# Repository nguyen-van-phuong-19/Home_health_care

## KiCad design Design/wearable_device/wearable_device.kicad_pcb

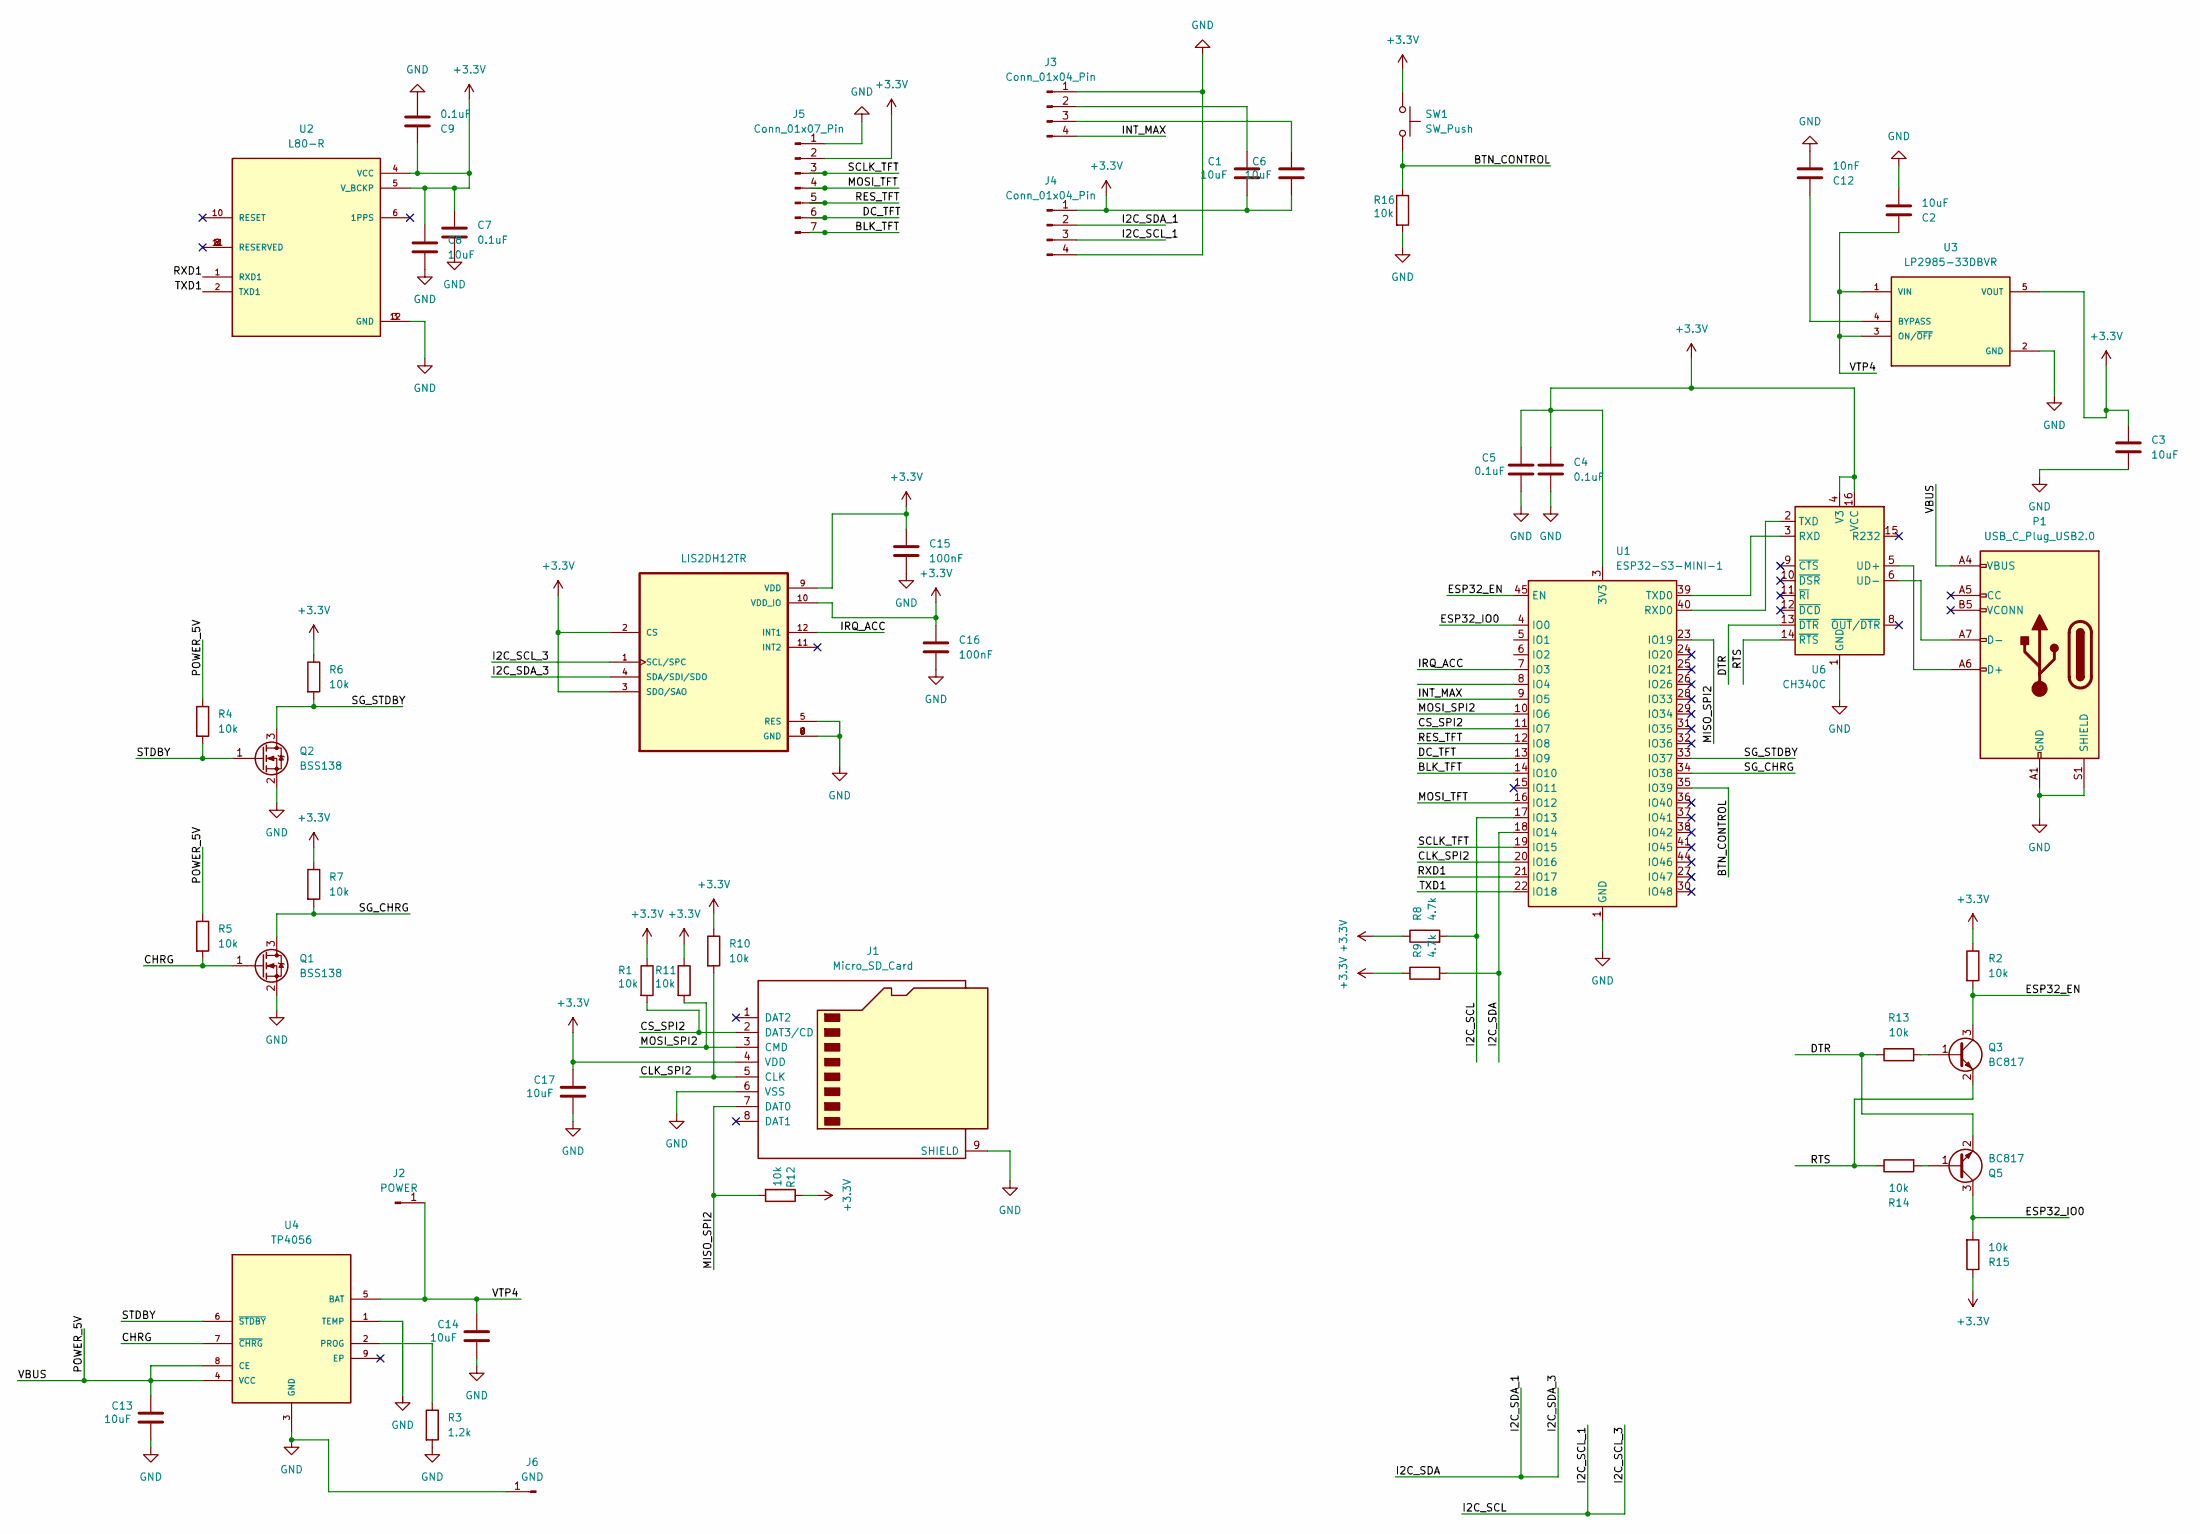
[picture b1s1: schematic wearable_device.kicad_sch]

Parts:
C1, C2, C3, C6, C8, C13, C14, C17: 10uF; C_0603_1608Metric
C4, C5, C7, C9: 0.1uF; C_0603_1608Metric
C12: 10nF; C_0603_1608Metric
C15, C16: 100nF; C_0603_1608Metric
J1: Micro_SD_Card; microSD_HC_Hirose_DM3D-SF
J2: POWER; PinHeader_1x01_P2.00mm_Vertical
J3, J4: Conn_01x04_Pin; PinHeader_1x04_P2.00mm_Vertical
J5: Conn_01x07_Pin; PinHeader_1x07_P2.54mm_Vertical
J6: GND; PinHeader_1x01_P2.00mm_Vertical
P1: USB_C_Plug_USB2.0; USB_C_Receptacle_GCT_USB4105-xx-A_16P_TopMnt_Horizontal
Q1, Q2: BSS138; SOT-23
Q3, Q5: BC817; SOT-23
R1, R2, R4, R5, R6, R7, R10, R11, R12, R13, R14, R15, R16: 10k; R_0603_1608Metric
R3: 1.2k; R_0603_1608Metric
R8, R9: 4.7k; R_0603_1608Metric
SW1: SW_Push; SW_Tactile_SPST_NO_Straight_CK_PTS636Sx25SMTRLFS
U1: ESP32-S3-MINI-1; ESP32-S2-MINI-1
U2: L80-R; XCVR_L80-R
U3: LP2985-33DBVR; SOT95P280X145-5N; PARTREV O
U4: TP4056; SOP127P600X175-9N
U5: LIS2DH12TR; PQFN50P200X200100-12N
U6: CH340C; SOIC-16_3.9x9.9mm_P1.27mm

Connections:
+3.3V: C1.2, C3.1, C4.1, C5.1, C6.2, C7.1, C8.1, C9.1, C15.1, C16.1, C17.1, J1.4 (VDD), J4.1, J5.2, R1.1, R2.1, R6.1, R7.1, R8.1, R9.1, R10.1, R11.1, R12.1, R15.1, SW1.1, U1.3 (3V3), U2.4 (VCC), U2.5 (V_BCKP), U3.5 (VOUT), U5.2 (CS), U5.3 (SDO/SAO), U5.9 (VDD), U5.10 (VDD_IO), U6.4 (V3), U6.16 (VCC)
/BLK_TFT: J5.7, U1.14 (IO10)
/BTN_CONTROL: R16.1, SW1.2, U1.35 (IO39)
/CHRG: Q1.1 (G), R5.2, U4.7 (~CHRG)
/CLK_SPI2: J1.5 (CLK), R10.2, U1.20 (IO16)
/CS_SPI2: J1.2 (DAT3/CD), R1.2, U1.11 (IO7)
/DC_TFT: J5.6, U1.13 (IO9)
/DTR: Q5.2 (E), R13.1, U6.13 (~DTR)
/ESP32_EN: Q3.3 (C), R2.2, U1.45 (EN)
/ESP32_IO0: Q5.3 (C), R15.2, U1.4 (IO0)
/I2C_SCL: J4.3, R8.2, U1.17 (IO13), U5.1 (SCL/SPC)
/I2C_SDA: J4.2, R9.2, U1.18 (IO14), U5.4 (SDA/SDI/SDO)
/INT_MAX: J3.4, U1.9 (IO5)
/IRQ_ACC: U1.7 (IO3), U5.12 (INT1)
/MISO_SPI2: J1.7 (DAT0), R12.2, U1.23 (IO19)
/MOSI_SPI2: J1.3 (CMD), R11.2, U1.10 (IO6)
/MOSI_TFT: J5.4, U1.16 (IO12)
/POWER_5V: C13.1, P1.A4 (VBUS), P1.A9 (VBUS), P1.B4 (VBUS), P1.B9 (VBUS), R4.1, R5.1, U4.4 (VCC), U4.8 (CE)
/RES_TFT: J5.5, U1.12 (IO8)
/RTS: Q3.2 (E), R14.1, U6.14 (~RTS)
/RXD1: U1.21 (IO17), U2.1 (RXD1)
/SCLK_TFT: J5.3, U1.19 (IO15)
/SG_CHRG: Q1.3 (D), R7.2, U1.34 (IO38)
/SG_STDBY: Q2.3 (D), R6.2, U1.33 (IO37)
/STDBY: Q2.1 (G), R4.2, U4.6 (~STDBY)
/TXD1: U1.22 (IO18), U2.2 (TXD1)
/VTP4: C2.1, C14.1, J2.1, U3.1 (VIN), U3.3 (ON/~OFF), U4.5 (BAT)
GND: C2.2, C3.2, C4.2, C5.2, C7.2, C8.2, C9.2, C12.2, C13.2, C14.2, C15.2, C16.2, C17.2, J1.6 (VSS), J1.9 (SHIELD), J3.1, J4.4, J5.1, J6.1, P1.A1 (GND), P1.A12 (GND), P1.B1 (GND), P1.B12 (GND), P1.S1 (SHIELD), Q1.2 (S), Q2.2 (S), R3.2, R16.2, U1.1 (GND), U1.2 (GND), U1.42 (GND), U1.43 (GND), U1.46 (GND), U1.47 (GND), U1.48 (GND), U1.49 (GND), U1.50 (GND), U1.51 (GND), U1.52 (GND), U1.53 (GND), U1.54 (GND), U1.55 (GND), U1.56 (GND), U1.57 (GND), U1.58 (GND), U1.59 (GND), U1.60 (GND), U1.61 (GND), U1.62 (GND), U1.63 (GND), U1.64 (GND), U1.65 (GND), U2.3 (GND), U2.12 (GND), U3.2 (GND), U4.1 (TEMP), U4.3 (GND), U5.5 (RES), U5.6 (GND), U5.7 (GND), U5.8 (GND), U6.1 (GND)
unnamed: C1.1, J3.2
unnamed: C6.1, J3.3
unnamed: P1.A6 (D+), U6.5 (UD+)
unnamed: P1.A7 (D-), U6.6 (UD-)
unnamed: Q3.1 (B), R13.2
unnamed: Q5.1 (B), R14.2
unnamed: U1.40 (RXD0), U6.2 (TXD)
unnamed: U1.39 (TXD0), U6.3 (RXD)
unnamed: C12.1, U3.4 (BYPASS)
unnamed: R3.1, U4.2 (PROG)

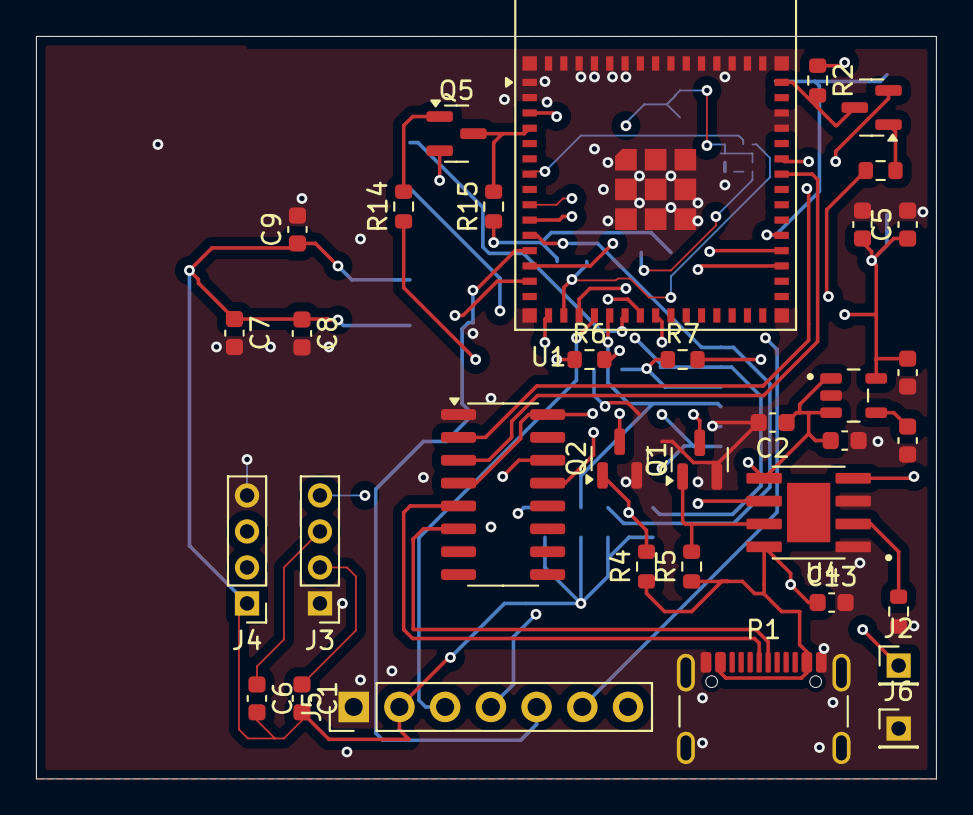
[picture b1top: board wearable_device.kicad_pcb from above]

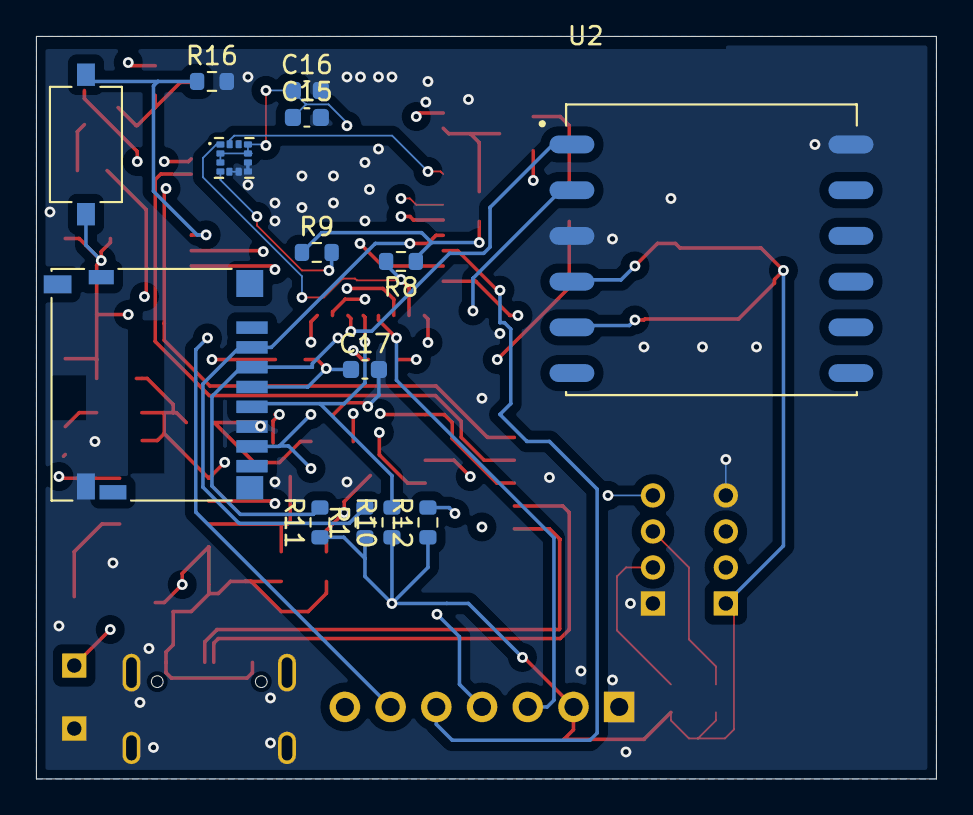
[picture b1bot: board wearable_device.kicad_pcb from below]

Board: 4 copper layers, 50.0 x 41.2 mm, 49 parts (14 on the bottom side), 38 nets.

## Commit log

2025-01-27 add documents form windown
    and add project to windown
2025-02-07 create server project
2025-02-07 add requirements context
2025-02-07 add gitignore file
2025-02-08 add openai library
2025-02-11 add 2 folder to github
2025-02-21 add design wearable device
2025-03-03 add design
2025-03-03 hello
2025-03-03 add .gitignore to exclude build artifacts and configuration files
2025-03-03 update .gitignore and add configuration files for Flutter application
2025-03-03 add STM32 board support files and update .gitignore
2025-03-04 update .gitignore to exclude Drivers directory and add license files for STM32 HAL drivers
2025-03-04 update .gitignore and add STM32 IDE configuration files
2025-04-12 complete design pcb board
2025-04-14 add test esp32-s3 board
2025-04-21 commint app android
2025-04-22 clean server
2025-04-22 add flutter_blue_background library for android app
2025-04-22 add function data_processing_from_LIS2DH12TR
2025-04-24 add wifi, ble, mqtt
2025-04-24 refactor: clean up MQTT and BLE integration, add high-level publish helpers
2025-04-24 feat: add BLE connection handling and notifications for sensor data
2025-04-25 feat: Integrate MQTT and BLE functionalities in the wearable app
    - Added MQTT event callback in wifi_pr.c for handling incoming messages.
    - Enhanced Wi-Fi initialization in wifi_pr.c with error handling and connection timeout.
    - Introduced a new partition table in partitions.csv for better memory management.
    - Updated sdkconfig to use the new custom partition table.
    - Refactored BLE service to use flutter_blue_plus for improved BLE operations.
    - Implemented BLE scanning and connection logic in the wearable app.
2025-04-27 feat: Add initial project structure with configuration files and Wi-Fi functionality
2025-04-27 feat: Implement BLE connection callback registration and handling
2025-04-27 feat: Add BLE service and characteristic UUIDs for heart rate, SpO2, accelerometer, and GPS
2025-04-27 feat: Enhance BLE functionality with event group handling for connection state
2025-04-27 refactor: Clean up commented code and improve logging in LIS2DH12TR initialization
2025-04-27 refactor: Remove unused Bluetooth imports and related variables in HomeScreen
2025-04-27 feat: Update BLE characteristic handles and modify notification function calls for heart rate, SpO2, and accelerometer
2025-04-27 refactor: Update commented code for GPS notification payload format
2025-04-27 feat: Implement BLE data processing service and integrate it into the main application flow
2025-04-27 fix: Update Firebase credential path to include 'env' directory
2025-04-27 feat: Refactor BLE initialization and connection handling in main app flow
2025-04-27 feat: Implement BLE foreground service and integrate with main application
2025-04-27 refactor: Update UUID definitions and improve BLE service initialization
2025-05-01 jncjdnv
2025-05-08 feat: Initialize wearable web application with Next.js and Tailwind CSS
    - Add package.json for project dependencies and scripts
    - Create PostCSS configuration for Tailwind CSS
    - Add SVG icons for UI components
    - Implement global CSS styles with Tailwind
    - Set up root layout and metadata for the application
    - Create main page with dynamic map and metrics display
2025-05-09 Add BLE service enhancements and update Android permissions
    - Introduced raw UUID data for advertising in BLE service.
    - Updated GATT characteristics to include access callbacks.
    - Enhanced BLE advertising parameters and added logging for connection RSSI.
    - Refactored BLE initialization and service discovery processes.
    - Updated AndroidManifest.xml to streamline permissions for Bluetooth and location services.
    - Integrated permission_handler package for better permission management.
2025-05-09 Refactor BLE advertising and connection handling
    - Updated advertising parameters to include device name in BLE advertising.
    - Removed unused characteristic UUIDs definition and related code.
    - Improved BLE sync callback for better clarity and organization.
    - Added a new getter for connection state in BleService to streamline connection state management.
    - Cleaned up commented-out code in the Flutter app for better readability.
    - Ensured proper handling of device connection state in the wearable app.
2025-05-10 feat: Refactor BLE service initialization and enhance data handling
2025-05-10 refactor: Remove unused BLE service imports from main.dart
2025-05-10 Xóa các tệp cấu hình và mã nguồn không còn sử dụng trong dự án phần cứng STM32, bao gồm các tệp .cproject, .mxproject, .project, và các tệp mã nguồn liên quan đến HAL và CMSIS. Thêm tệp compile_comma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
2025-05-11 refactor: Cập nhật cấu trúc mã nguồn và cải thiện quản lý dữ liệu cảm biến
    - Xóa các tùy chọn Bluetooth không cần thiết trong sdkconfig.
    - Tối ưu hóa mã nguồn trong hello_world.c để chỉ in ra "Hello, world!" mỗi giây.
    - Thêm tệp CMakeLists.txt cho dự án main_hardware và cấu hình sdkconfig mới.
    - Tạo mới các tệp mã nguồn cho BLE, cảm biến và MQTT, bao gồm các hàm khởi tạo và quản lý dữ liệu.
    - Cải thiện khả năng xử lý dữ liệu cảm biến và tích hợp với MQTT để gửi dữ liệu.
    - Cập nhật các tệp CMakeLists.txt để bao gồm các tệp mã nguồn mới.
2025-05-11 refactor: Cập nhật mã nguồn MQTT và cải thiện quản lý dữ liệu
    - Thêm thư viện string.h để sử dụng các hàm xử lý chuỗi.
    - Cải thiện cách gọi hàm mqtt_subscribe_topic bằng cách loại bỏ ESP_ERROR_CHECK.
    - Cập nhật các định nghĩa topic MQTT để phù hợp với cấu trúc mới.
    - Loại bỏ trường port không cần thiết trong cấu hình MQTT.
    - Cải thiện định dạng payload trong các hàm publish để loại bỏ timestamp không cần thiết.
    - Cập nhật các biến và cấu trúc liên quan đến Wi-Fi và MQTT để tối ưu hóa hiệu suất.
2025-05-11 refactor: Cập nhật mã nguồn MQTT bằng cách loại bỏ các hàm không cần thiết và cải thiện định dạng payload
2025-05-11 refactor: Improve BLE data handling and publish via MQTT
2025-05-11 refactor: Update sensor data handling and improve motion data type in BLE communication
2025-05-12 refactor: Add L80-R GNSS module support with UART initialization and NMEA parsing
2025-05-14 edit design
2025-05-15 refactor: Update L80-R GNSS module integration and enhance data handling in Firebase and MQTT
2025-05-15 refactor: Enhance authentication flow with Google sign-in and update Firebase options
2025-05-15 refactor: Enhance HomeScreen with user info dialog and sign-out functionality
2025-05-16 Refactor hardware and software components for ST7789 LCD integration and Firebase authentication
    - Updated I2C configuration in main.h for ESP32-S3-N16R8.
    - Added TFT task for ST7789 display initialization and rendering in main_hardware.c.
    - Implemented ST7789 LCD driver in st7789_lcd.c and st7789_lcd.h, including basic drawing functions.
    - Modified transmit_task in test_esp.c to use dynamic user ID from Firebase authentication.
    - Updated Firebase options in firebase_options.dart with new client IDs.
    - Removed old firebase_options.dart file and ensured new options are utilized in the app.
2025-05-16 refactor: Clean up AndroidManifest.xml and update dependencies in build.gradle.kts and pubspec.lock
2025-05-16 refactor: Update Wi-Fi connection handling and integrate dynamic user ID in data publishing
2025-05-23 Add SSD1306 OLED display driver and integrate into ESP32 project
    - Created ssd1306_oled.h for SSD1306 OLED display driver with I2C configuration and function prototypes.
    - Updated test_esp.c to include SSD1306 initialization and drawing functions (commented out for future use).
    - Modified wifi_pr.c to change WiFi password for network "102".
    - Updated create_example.py to generate sample data for a new user ID.
    - Refactored process_ble_data.dart to improve BLE data processing structure.
    - Enhanced history_screen.dart to implement scrolling behavior for heart rate and SpO2 history.
2025-05-23 feat: Enhance BLE functionality and calorie tracking
    - Added BLE service to handle ESP32-S3 advertisements and phone data broadcasting.
    - Implemented calorie calculation based on heart rate and motion data.
    - Introduced sleep hours tracking and MQTT integration for calories and sleep data.
    - Updated sensor data management to include daily calorie totals and NVS persistence.
    - Modified main application logic to accommodate new BLE and sensor functionalities.
    - Improved AndroidManifest.xml for foreground service permissions.
2025-05-27 feat: Implement calorie tracking and MQTT integration for wearable app
2025-06-01 cajbvjadbvj
2025-06-03 edit document
2025-06-05 Update wearable app paths
2025-06-05 ahdbvhad
2025-06-05 Add sleep status tracking
2025-06-05 edit logic for sleep time
2025-06-05 edit logic server
2025-06-05 Load sleep duration on startup
2025-06-05 ajhdbvjhsdv
2025-06-05 Add now_time support for daily sleep
2025-06-06 add debug log
2025-06-06 add document
2025-06-06 hdbvhsdv
2025-06-22 update documents
2025-08-08 feat: add gemini based report and qa
